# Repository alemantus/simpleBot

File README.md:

# simpleBot
 Simple robot with 2 wheels and a castor wheel

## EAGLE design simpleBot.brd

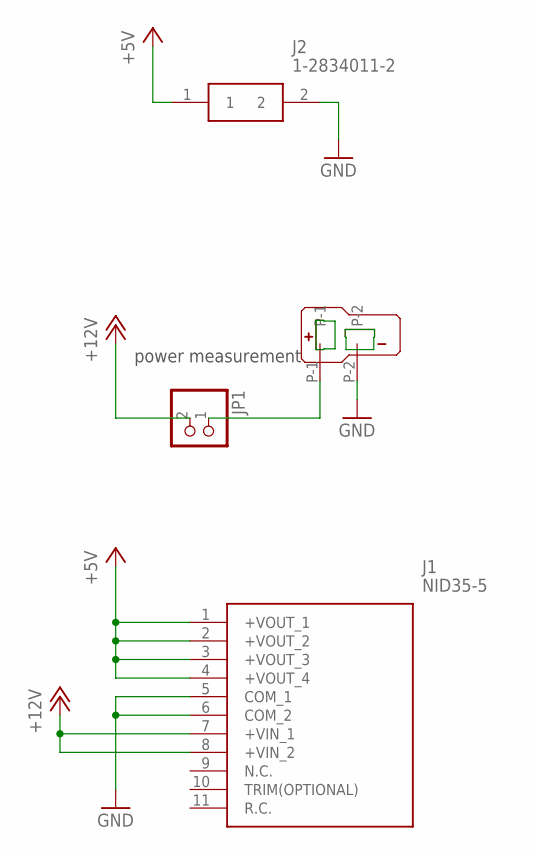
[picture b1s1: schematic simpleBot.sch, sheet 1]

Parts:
J1: NID35-5; NID355
J2: 1-2834011-2; 128340112
JP1: PINHD-1X2; 1X02
U$2: T-PLUG_CONNECTOR; T_PLUG_CONNECTOR

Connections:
+5V: J1.1 (+VOUT_1), J1.2 (+VOUT_2), J1.3 (+VOUT_3), J1.4 (+VOUT_4), J2.1
+12V: J1.7 (+VIN_1), J1.8 (+VIN_2), JP1.2
GND: J1.5 (COM_1), J1.6 (COM_2), J2.2, U$2.P-2; also elsewhere on the board
unnamed: JP1.1, U$2.P-1

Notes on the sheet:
power measurement

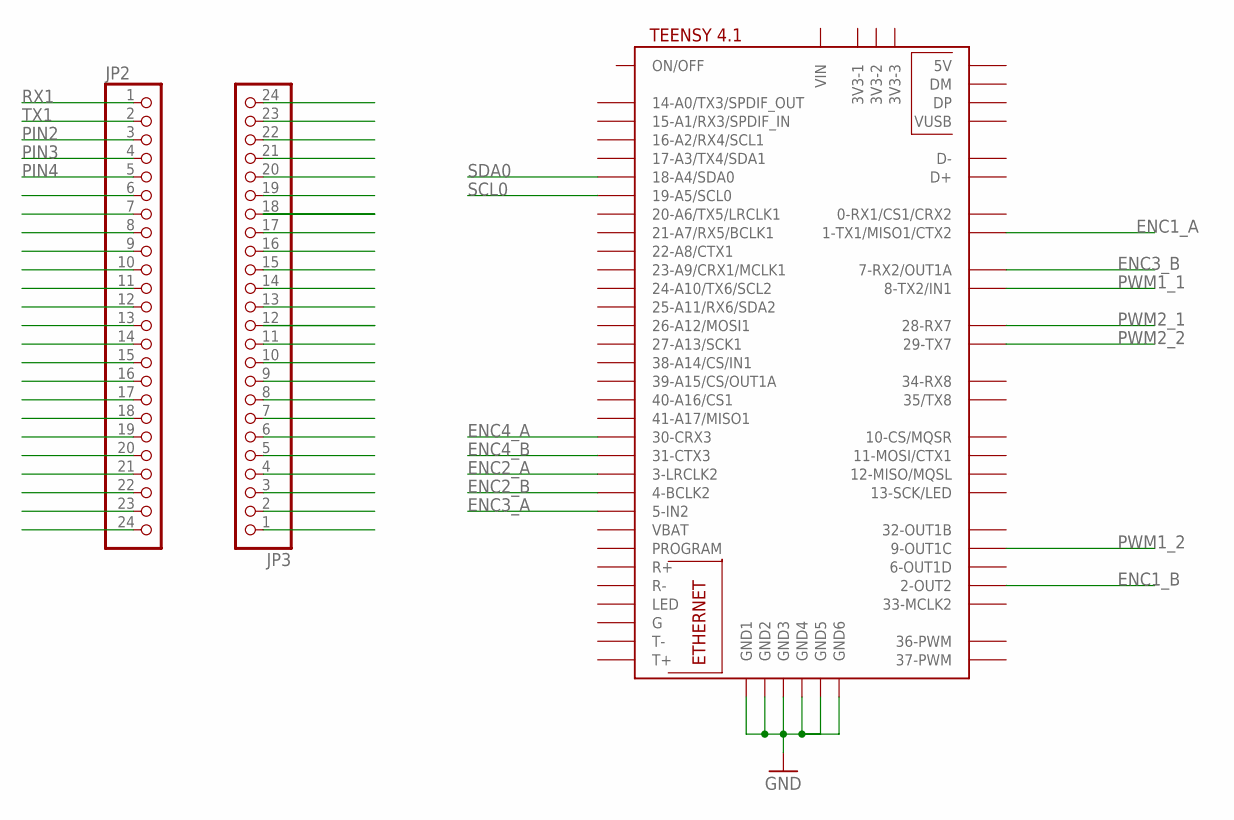
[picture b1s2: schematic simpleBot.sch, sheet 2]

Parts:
JP2, JP3: PINHD-1X24; 1X24
U$1: TEENSY41

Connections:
ENC1_A: U$1.1-TX1/MISO1/CTX2
ENC1_B: U$1.2-OUT2
ENC2_A: U$1.3-LRCLK2
ENC2_B: U$1.4-BCLK2
ENC3_A: U$1.5-IN2
ENC3_B: U$1.7-RX2/OUT1A
ENC4_A: U$1.30-CRX3
ENC4_B: U$1.31-CTX3
GND: U$1.GND1, U$1.GND2, U$1.GND3, U$1.GND4, U$1.GND5, U$1.GND6; also elsewhere on the board
PIN2: JP2.3
PIN3: JP2.4
PIN4: JP2.5
PWM1_1: U$1.8-TX2/IN1
PWM1_2: U$1.9-OUT1C
PWM2_1: U$1.28-RX7
PWM2_2: U$1.29-TX7
RX1: JP2.1
SCL0: U$1.19-A5/SCL0
SDA0: U$1.18-A4/SDA0
TX1: JP2.2

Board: 2 copper layers, 7 parts (0 on the bottom side), 4 nets, no tracks yet.

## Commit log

2022-01-02 uploaded eagel files
    eagle files are not finished
2022-03-15 added a working encoder example
    working PID on one motor
2022-03-21 merged jetson code with repo
2022-03-21 removed dot from filename
2022-03-21 added catkin_ws to repo
2022-03-21 started cmd/vel implemt
2022-04-04 A lot of changes
2022-07-06 small config change
2022-08-13 publishing image with features and mask
2022-08-13 threshold are now set as parameters
2022-08-17 image pric can now follow right or left line
2022-08-17 can also follow a line with no splits
2022-08-17 cross detection works well
2022-08-17 removed unused node
2022-08-17 removed broken folder
2022-08-17 added jetson nano camera node
2022-08-17 works again
2022-08-17 moved catkin_ws to ROS folder
2022-08-19 uncommented power monitor code
2022-08-19 added credits to odom
2022-08-19 moved platformIO project to Teensy folder
